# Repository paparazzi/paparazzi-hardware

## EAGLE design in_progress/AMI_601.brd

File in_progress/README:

This directory contains in progress project an some finished development board I made to test different parts

adxrs300_breakout.sch : breakout board for adxrs300 gyro evaluation
AMI_601.sch : breakout board for AMI601 magnetometer
current_probe.sch : some current sensor I don't remember about
ir_single_long.sch
ir_single_slim.sch
lipo_connector.sch
olimex_add_on.sch
pth_supply.sch
pth_supply_servos_molex.sch
pth_supply_servos.sch
test_2620.sch
test_filter.sch
test_usb_hub.sch
tiny4l_18_1_99.sch
vor_add_on.sch
xbee.sch

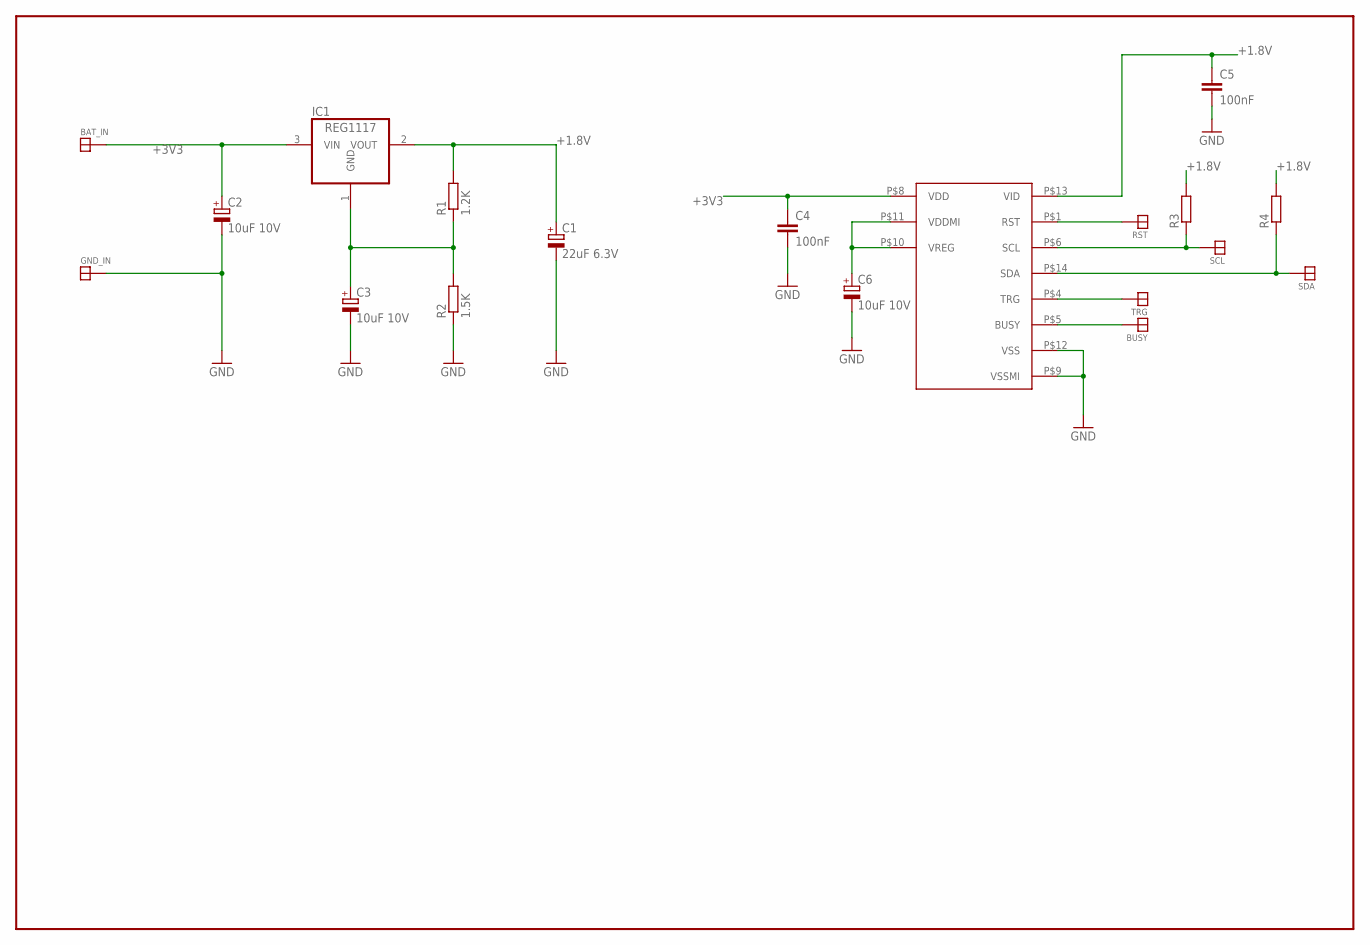
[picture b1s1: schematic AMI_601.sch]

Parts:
BAT_IN: SOLDER_PAD150_75; SOLD_PAD_150_75
BUSY: SOLDER_PAD150_75; SOLD_PAD_150_75
C1: 22uF 6.3V; CT3528
C2, C3, C6: 10uF 10V; CT3216
C4, C5: 100nF; C0805K
GND_IN: SOLDER_PAD150_75; SOLD_PAD_150_75
IC1: REG1117; SOT223
R1: 1.2K; M0805
R2: 1.5K; M0805
R3, R4: R-EU_M0805; M0805
RST: SOLDER_PAD150_75; SOLD_PAD_150_75
SCL: SOLDER_PAD150_75; SOLD_PAD_150_75
SDA: SOLDER_PAD150_75; SOLD_PAD_150_75
TRG: SOLDER_PAD150_75; SOLD_PAD_150_75
U$1: AMI601; AMI_601

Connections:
+1.8V: C1.+, C5.1, IC1.2 (VOUT), R1.2, R3.2, R4.2, U$1.P$13 (VID)
+3V3: BAT_IN.P$1, C2.+, C4.1, IC1.3 (VIN), U$1.P$8 (VDD)
GND: C1.-, C2.-, C3.-, C4.2, C5.2, C6.-, GND_IN.P$1, R2.1, U$1.P$9 (VSSMI), U$1.P$12 (VSS)
unnamed: C3.+, IC1.1 (GND), R1.1, R2.2
unnamed: C6.+, U$1.P$10 (VREG), U$1.P$11 (VDDMI)
unnamed: RST.P$1, U$1.P$1 (RST)
unnamed: R3.1, SCL.P$1, U$1.P$6 (SCL)
unnamed: R4.1, SDA.P$1, U$1.P$14 (SDA)
unnamed: TRG.P$1, U$1.P$4 (TRG)
unnamed: BUSY.P$1, U$1.P$5 (BUSY)

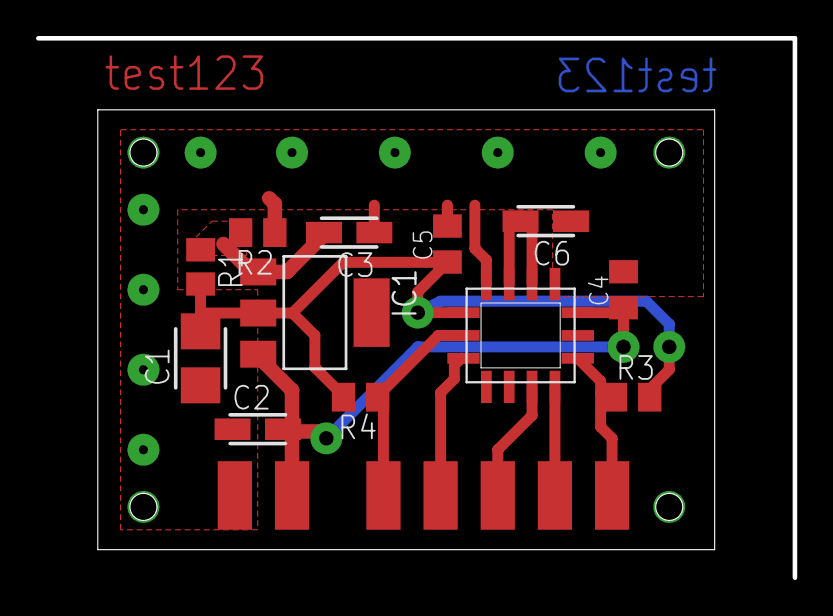
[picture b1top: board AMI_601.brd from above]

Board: 2 copper layers, 34.3 x 24.4 mm, 19 parts (0 on the bottom side), 10 nets.

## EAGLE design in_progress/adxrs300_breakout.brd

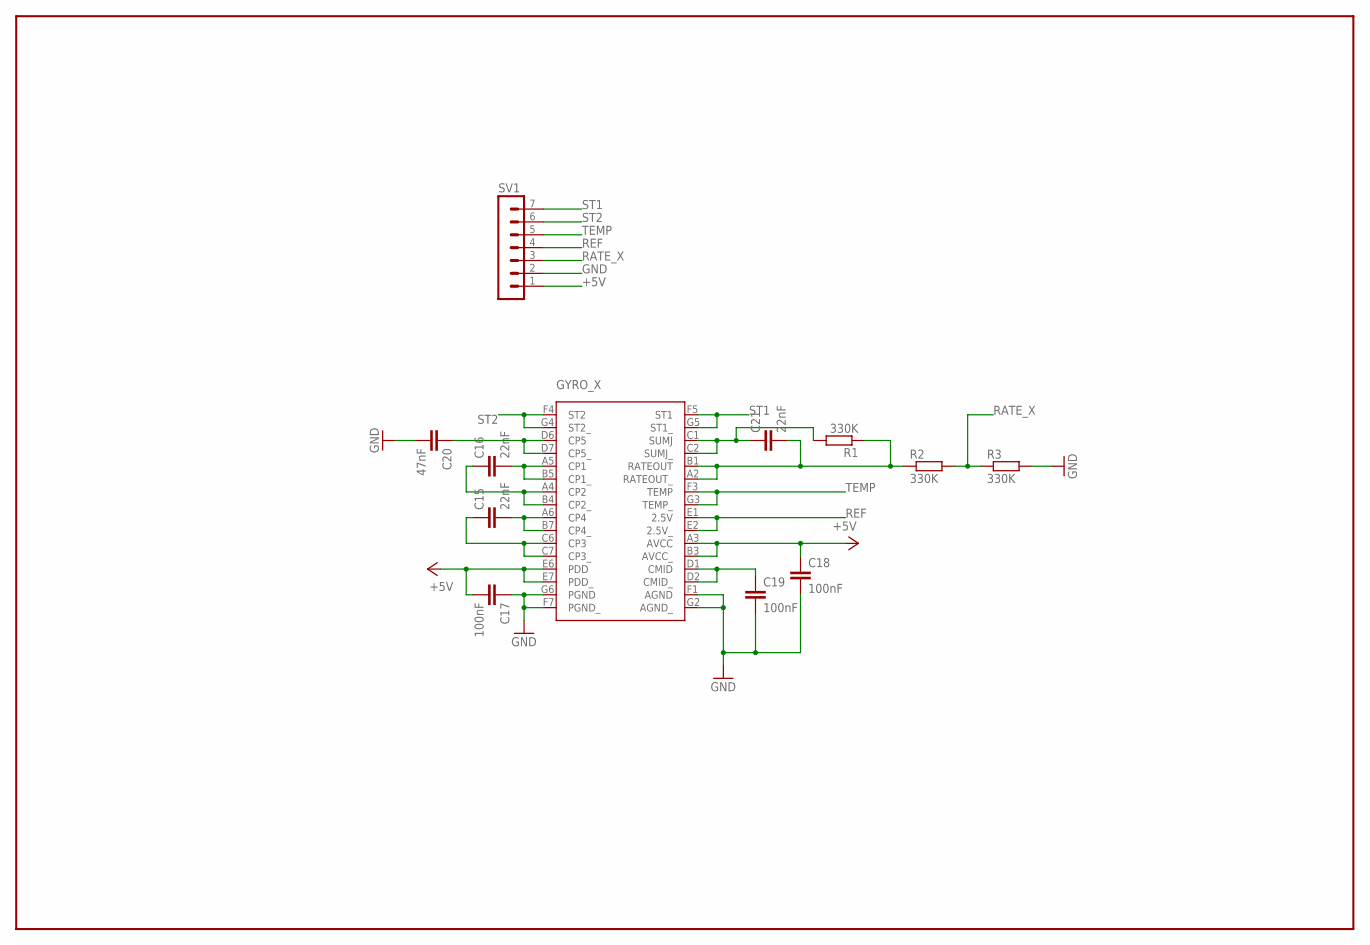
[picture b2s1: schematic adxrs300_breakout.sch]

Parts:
C15, C16, C21: 22nF; C0603K
C17, C18, C19: 100nF; C0603K
C20: 47nF; C0603K
GYRO_X: ADXR; BC-32
R1, R2, R3: 330K; R0603
SV1: MA07-1

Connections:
+5V: C17.2, C18.1, GYRO_X.A3 (AVCC), GYRO_X.B3 (AVCC_), GYRO_X.E6 (PDD), GYRO_X.E7 (PDD_), SV1.1
GND: C17.1, C18.2, C19.2, C20.2, GYRO_X.F1 (AGND), GYRO_X.F7 (PGND_), GYRO_X.G2 (AGND_), GYRO_X.G6 (PGND), R3.2, SV1.2
unnamed: C21.1, GYRO_X.C1 (SUMJ), GYRO_X.C2 (SUMJ_), R1.2
unnamed: C15.1, GYRO_X.C6 (CP3), GYRO_X.C7 (CP3_)
unnamed: C20.1, GYRO_X.D6 (CP5), GYRO_X.D7 (CP5_)
unnamed: C16.2, GYRO_X.A5 (CP1), GYRO_X.B5 (CP1_)
unnamed: C16.1, GYRO_X.A4 (CP2), GYRO_X.B4 (CP2_)
unnamed: C15.2, GYRO_X.A6 (CP4), GYRO_X.B7 (CP4_)
unnamed: C19.1, GYRO_X.D1 (CMID), GYRO_X.D2 (CMID_)
RATE_5V: C21.2, GYRO_X.A2 (RATEOUT_), GYRO_X.B1 (RATEOUT), R1.1, R2.1
RATE_X: R2.2, R3.1, SV1.3
REF: GYRO_X.E1 (2.5V), GYRO_X.E2 (2.5V_), SV1.4
ST1: GYRO_X.F5 (ST1), GYRO_X.G5 (ST1_), SV1.7
ST2: GYRO_X.F4 (ST2), GYRO_X.G4 (ST2_), SV1.6
TEMP: GYRO_X.F3 (TEMP), GYRO_X.G3 (TEMP_), SV1.5

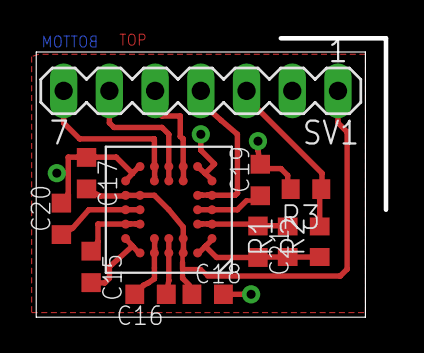
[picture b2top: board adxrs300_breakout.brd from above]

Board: 4 copper layers, 19.4 x 15.5 mm, 12 parts (0 on the bottom side), 15 nets.

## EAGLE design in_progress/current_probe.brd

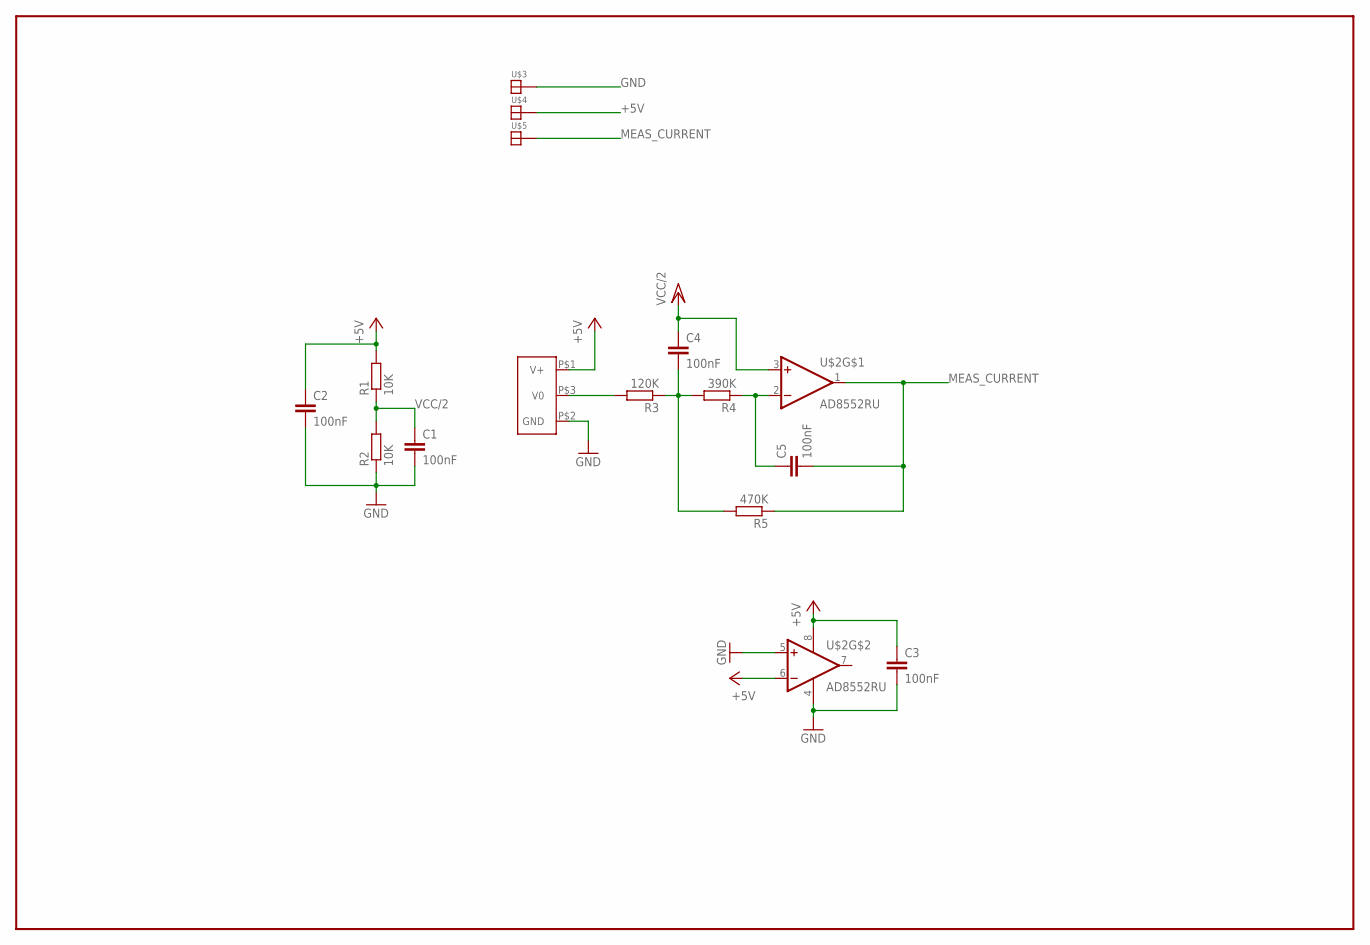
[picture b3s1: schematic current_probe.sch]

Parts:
C1, C2, C3, C4, C5: 100nF; C0603K
R1, R2: 10K; R0603
R3: 120K; R0603
R4: 390K; R0603
R5: 470K; R0603
U$1: SS495S; SS495SND
U$2: AD8552RU; TSSOP8
U$3, U$4, U$5: SOLDER_PAD100_50; SOLDER_PAD_100_50

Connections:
+5V: C2.1, C3.1, R1.2, U$1.P$1 (V+), U$2.6 (-IN), U$2.8 (V+), U$4.P$1
GND: C1.2, C2.2, C3.2, R2.1, U$1.P$2 (GND), U$2.4 (V-), U$2.5 (+IN), U$3.P$1
MEAS_CURRENT: C5.2, R5.1, U$2.1 (OUT), U$5.P$1
unnamed: R3.2, U$1.P$3 (V0)
unnamed: C4.2, R3.1, R4.2, R5.2
unnamed: C5.1, R4.1, U$2.2 (-IN)
VCC/2: C1.1, C4.1, R1.1, R2.2, U$2.3 (+IN)

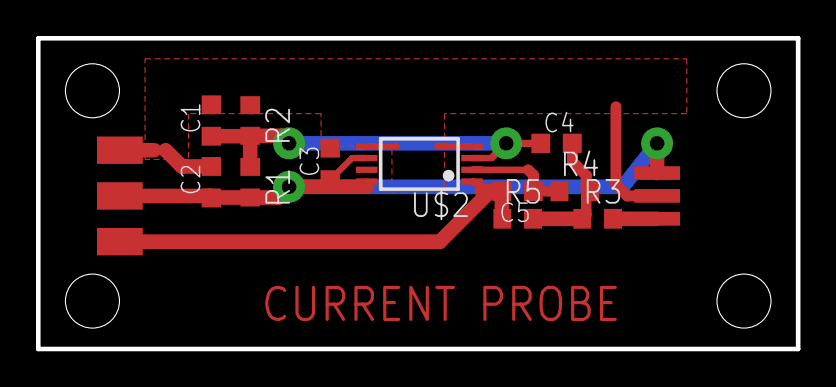
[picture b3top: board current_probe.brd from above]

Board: 2 copper layers, 42.2 x 17.3 mm, 15 parts (0 on the bottom side), 7 nets.

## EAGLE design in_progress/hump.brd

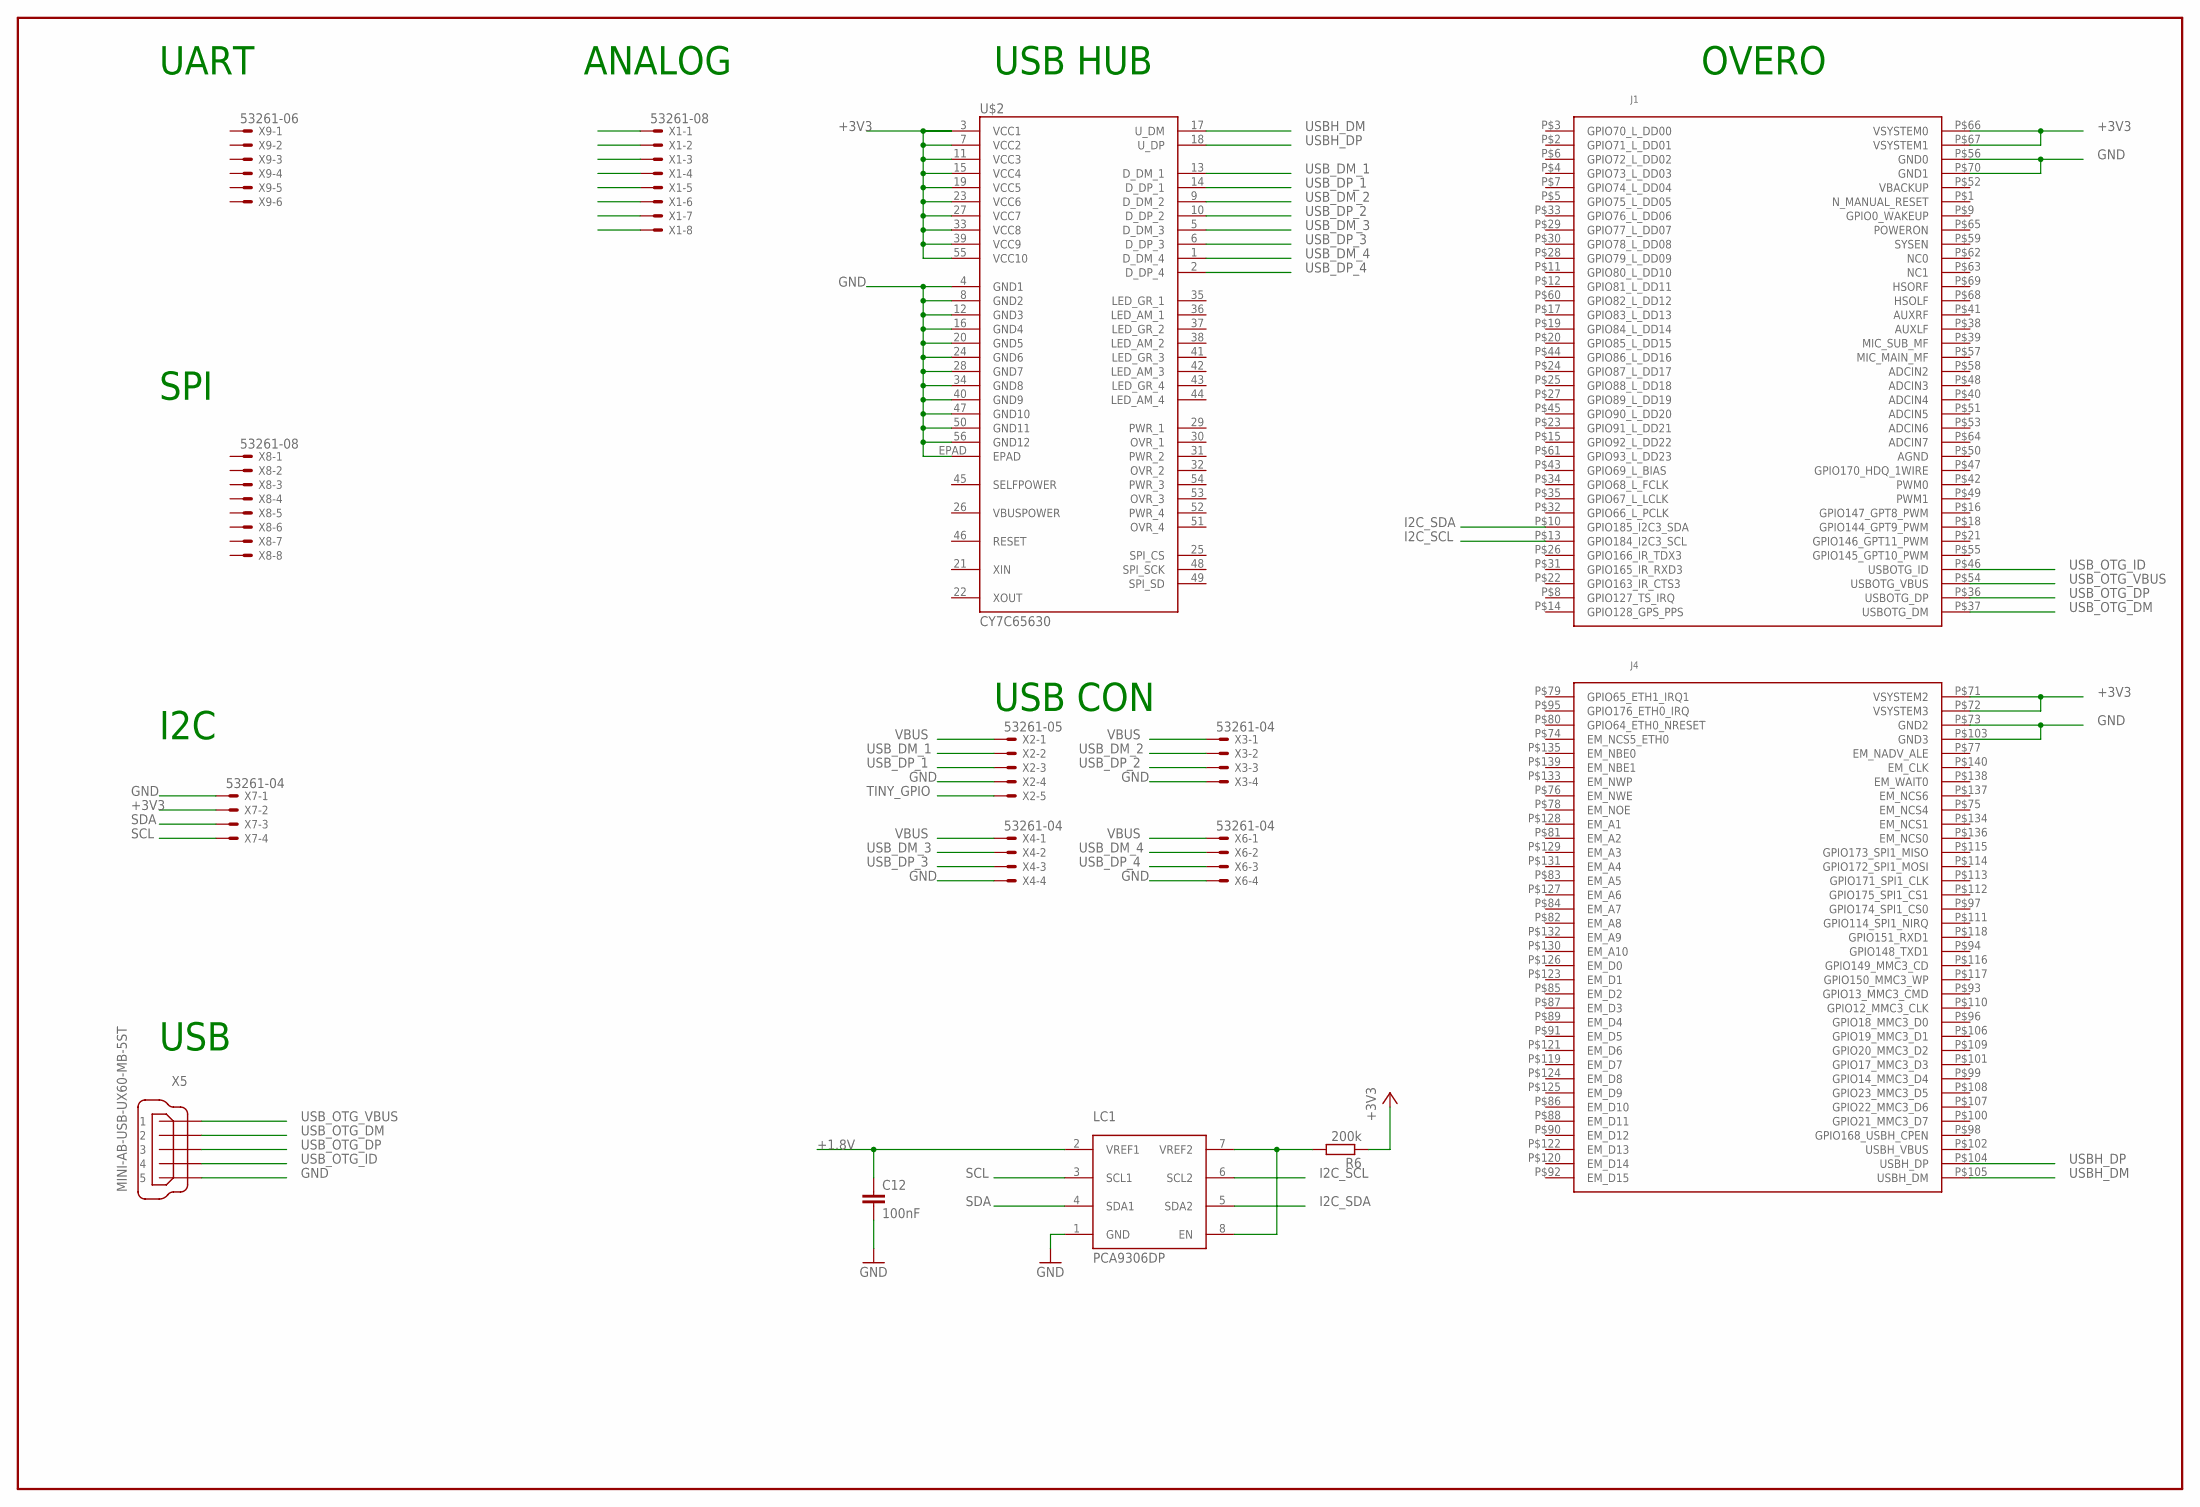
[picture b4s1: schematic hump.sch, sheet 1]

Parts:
C12: 100nF; C0603
LC1: PCA9306DP; TSSOP_B3
R6: 200k; R0603
U$1: CON_OVERO
U$2: CY7C65630; QFN56
X1, X8: 53261-08
X2: 53261-05
X3, X4, X6, X7: 53261-04
X5: MINI-AB-USB-UX60-MB-5ST; UX60-MB-5ST
X9: 53261-06

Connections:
+1.8V: C12.1, LC1.2 (VREF1)
+3V3: R6.1, U$1.P$66 (VSYSTEM0), U$1.P$67 (VSYSTEM1), U$1.P$71 (VSYSTEM2), U$1.P$72 (VSYSTEM3), U$2.3 (VCC1), U$2.7 (VCC2), U$2.11 (VCC3), U$2.15 (VCC4), U$2.19 (VCC5), U$2.23 (VCC6), U$2.27 (VCC7), U$2.33 (VCC8), U$2.39 (VCC9), U$2.55 (VCC10), X7.2
GND: C12.2, LC1.1 (GND), U$1.P$56 (GND0), U$1.P$70 (GND1), U$1.P$73 (GND2), U$1.P$103 (GND3), U$2.4 (GND1), U$2.8 (GND2), U$2.12 (GND3), U$2.16 (GND4), U$2.20 (GND5), U$2.24 (GND6), U$2.28 (GND7), U$2.34 (GND8), U$2.40 (GND9), U$2.47 (GND10), U$2.50 (GND11), U$2.56 (GND12), U$2.EPAD, X1.1, X2.4, X3.4, X4.4, X5.5, X6.4, X7.1; also elsewhere on the board
I2C_SCL: LC1.6 (SCL2), U$1.P$13 (GPIO184_I2C3_SCL)
I2C_SDA: LC1.5 (SDA2), U$1.P$10 (GPIO185_I2C3_SDA)
unnamed: LC1.7 (VREF2), LC1.8 (EN), R6.2
SCL: LC1.3 (SCL1), X7.4
SDA: LC1.4 (SDA1), X7.3
TINY_GPIO: X2.5
USBH_DM: U$1.P$105 (USBH_DM), U$2.17 (U_DM)
USBH_DP: U$1.P$104 (USBH_DP), U$2.18 (U_DP)
USB_DM_1: U$2.13 (D_DM_1), X2.2
USB_DM_2: U$2.9 (D_DM_2), X3.2
USB_DM_3: U$2.5 (D_DM_3), X4.2
USB_DM_4: U$2.1 (D_DM_4), X6.2
USB_DP_1: U$2.14 (D_DP_1), X2.3
USB_DP_2: U$2.10 (D_DP_2), X3.3
USB_DP_3: U$2.6 (D_DP_3), X4.3
USB_DP_4: U$2.2 (D_DP_4), X6.3
USB_OTG_DM: U$1.P$37 (USBOTG_DM), X5.2
USB_OTG_DP: U$1.P$36 (USBOTG_DP), X5.3
USB_OTG_ID: U$1.P$46 (USBOTG_ID), X5.4
USB_OTG_VBUS: U$1.P$54 (USBOTG_VBUS), X5.1
VBUS: X2.1, X3.1, X4.1, X6.1

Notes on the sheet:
OVERO
UART
SPI
I2C
USB
ANALOG
USB HUB
USB CON

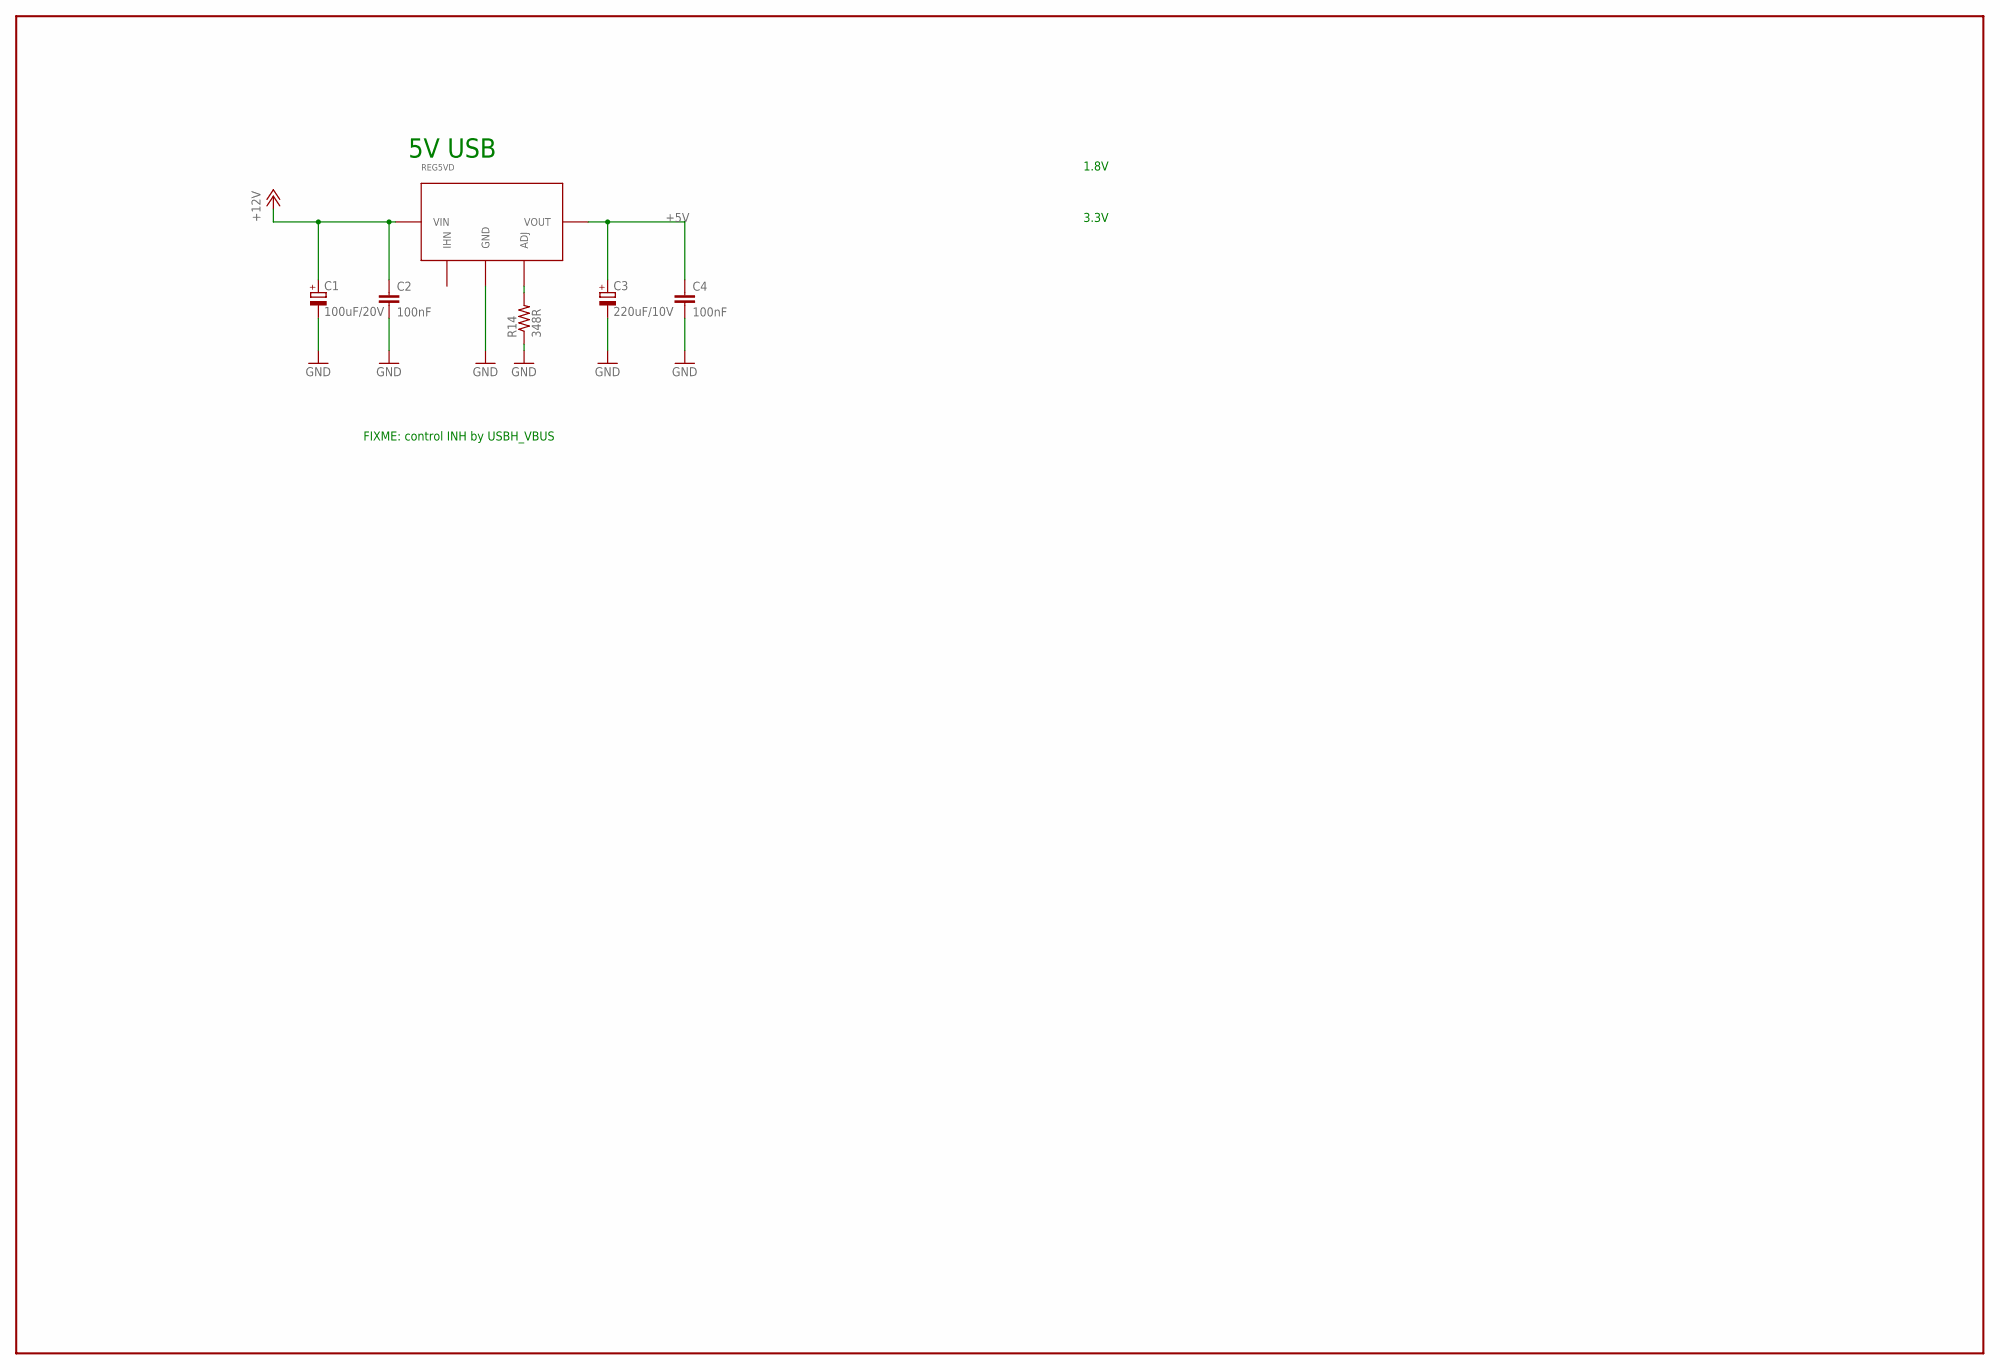
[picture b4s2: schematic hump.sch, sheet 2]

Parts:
C1: 100uF/20V; SMC_D
C2, C4: 100nF; C0603
C3: 220uF/10V; SMC_D
R14: 348R; R0603
REG5VD: PTHTH; PTH_TH

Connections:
+5V: C3.+, C4.1, REG5VD.P$3 (VOUT)
+12V: C1.+, C2.1, REG5VD.P$1 (VIN)
GND: C1.-, C2.2, C3.-, C4.2, R14.1, REG5VD.P$2 (GND); also elsewhere on the board
unnamed: R14.2, REG5VD.P$4 (ADJ)

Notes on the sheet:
5V USB
FIXME: control INH by USBH_VBUS
1.8V
3.3V

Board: 2 copper layers, 20 parts (0 on the bottom side), 26 nets, no tracks yet.

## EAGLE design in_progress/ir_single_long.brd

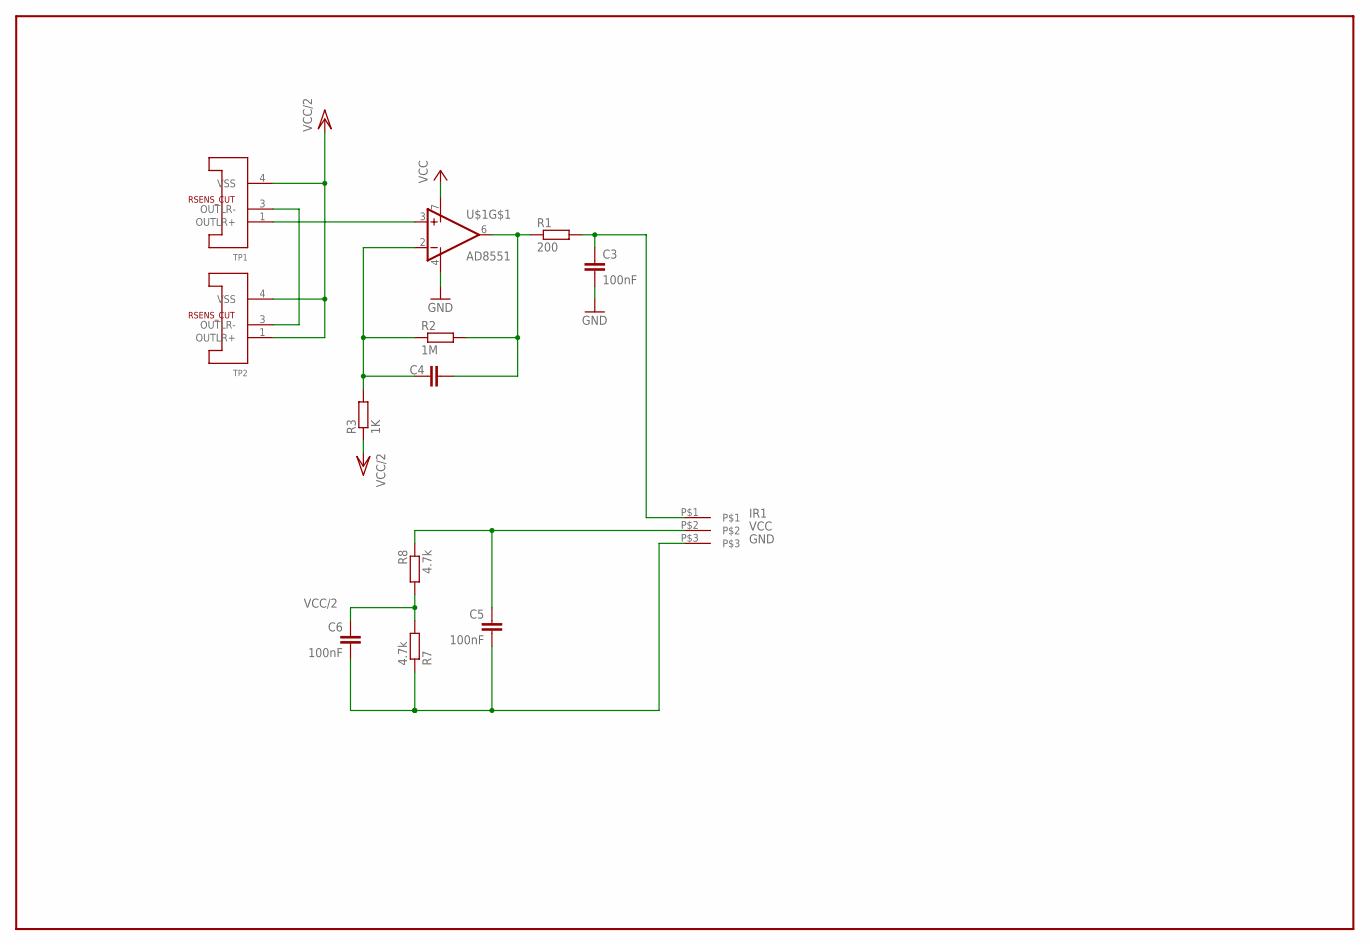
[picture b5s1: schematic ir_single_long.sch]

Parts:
C3: 100nF; C1206K
C4: C-EUC0603; C0603
C5, C6: 100nF; C0603
R1: 200; R0603
R2: 1M; R0603
R3: 1K; R0603
R7, R8: 4.7k; R0603
TP1, TP2: MLX90247SMD_LONG; T0_39_SMD_LONG
U$1: AD8551; MSOP8
U$2: SOLD_PAD_3; SOLD_PAD_2MM_3

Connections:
GND: C3.2, C5.2, C6.2, R7.1, U$1.4 (V-), U$2.P$3
IR1: C3.1, R1.2, U$2.P$1
unnamed: TP1.3 (OUTLR-), TP2.3 (OUTLR-)
unnamed: C4.2, R1.1, R2.2, U$1.6 (OUT)
unnamed: TP1.1 (OUTLR+), U$1.3 (+IN)
unnamed: C4.1, R2.1, R3.2, U$1.2 (-IN)
VCC: C5.1, R8.1, U$1.7 (V+), U$2.P$2
VCC/2: C6.1, R3.1, R7.2, R8.2, TP1.4 (VSS), TP2.1 (OUTLR+), TP2.4 (VSS)

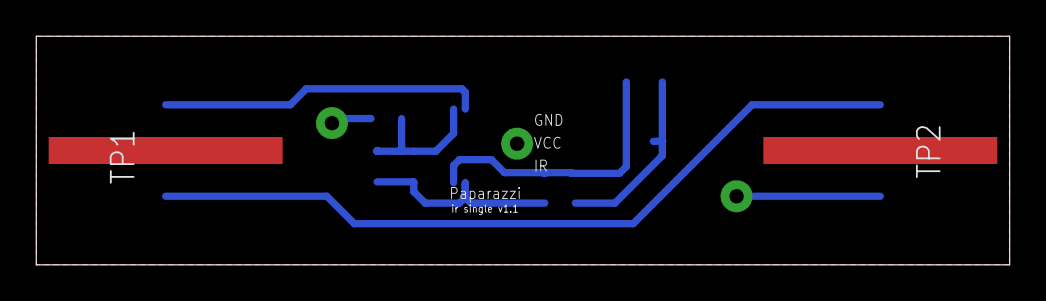
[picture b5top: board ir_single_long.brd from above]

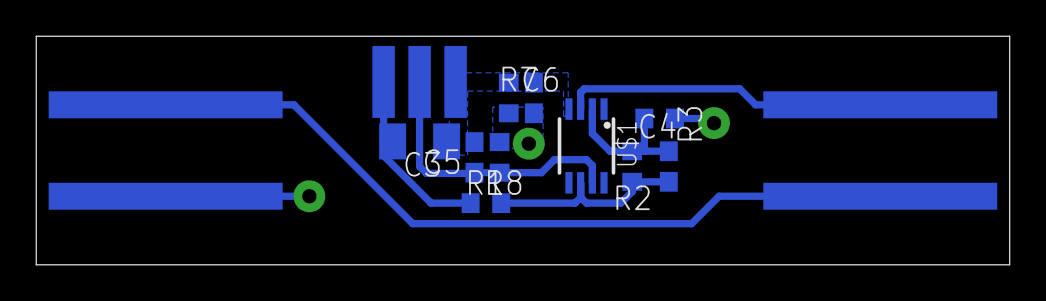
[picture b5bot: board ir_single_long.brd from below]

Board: 2 copper layers, 54.1 x 12.7 mm, 13 parts (11 on the bottom side), 8 nets.

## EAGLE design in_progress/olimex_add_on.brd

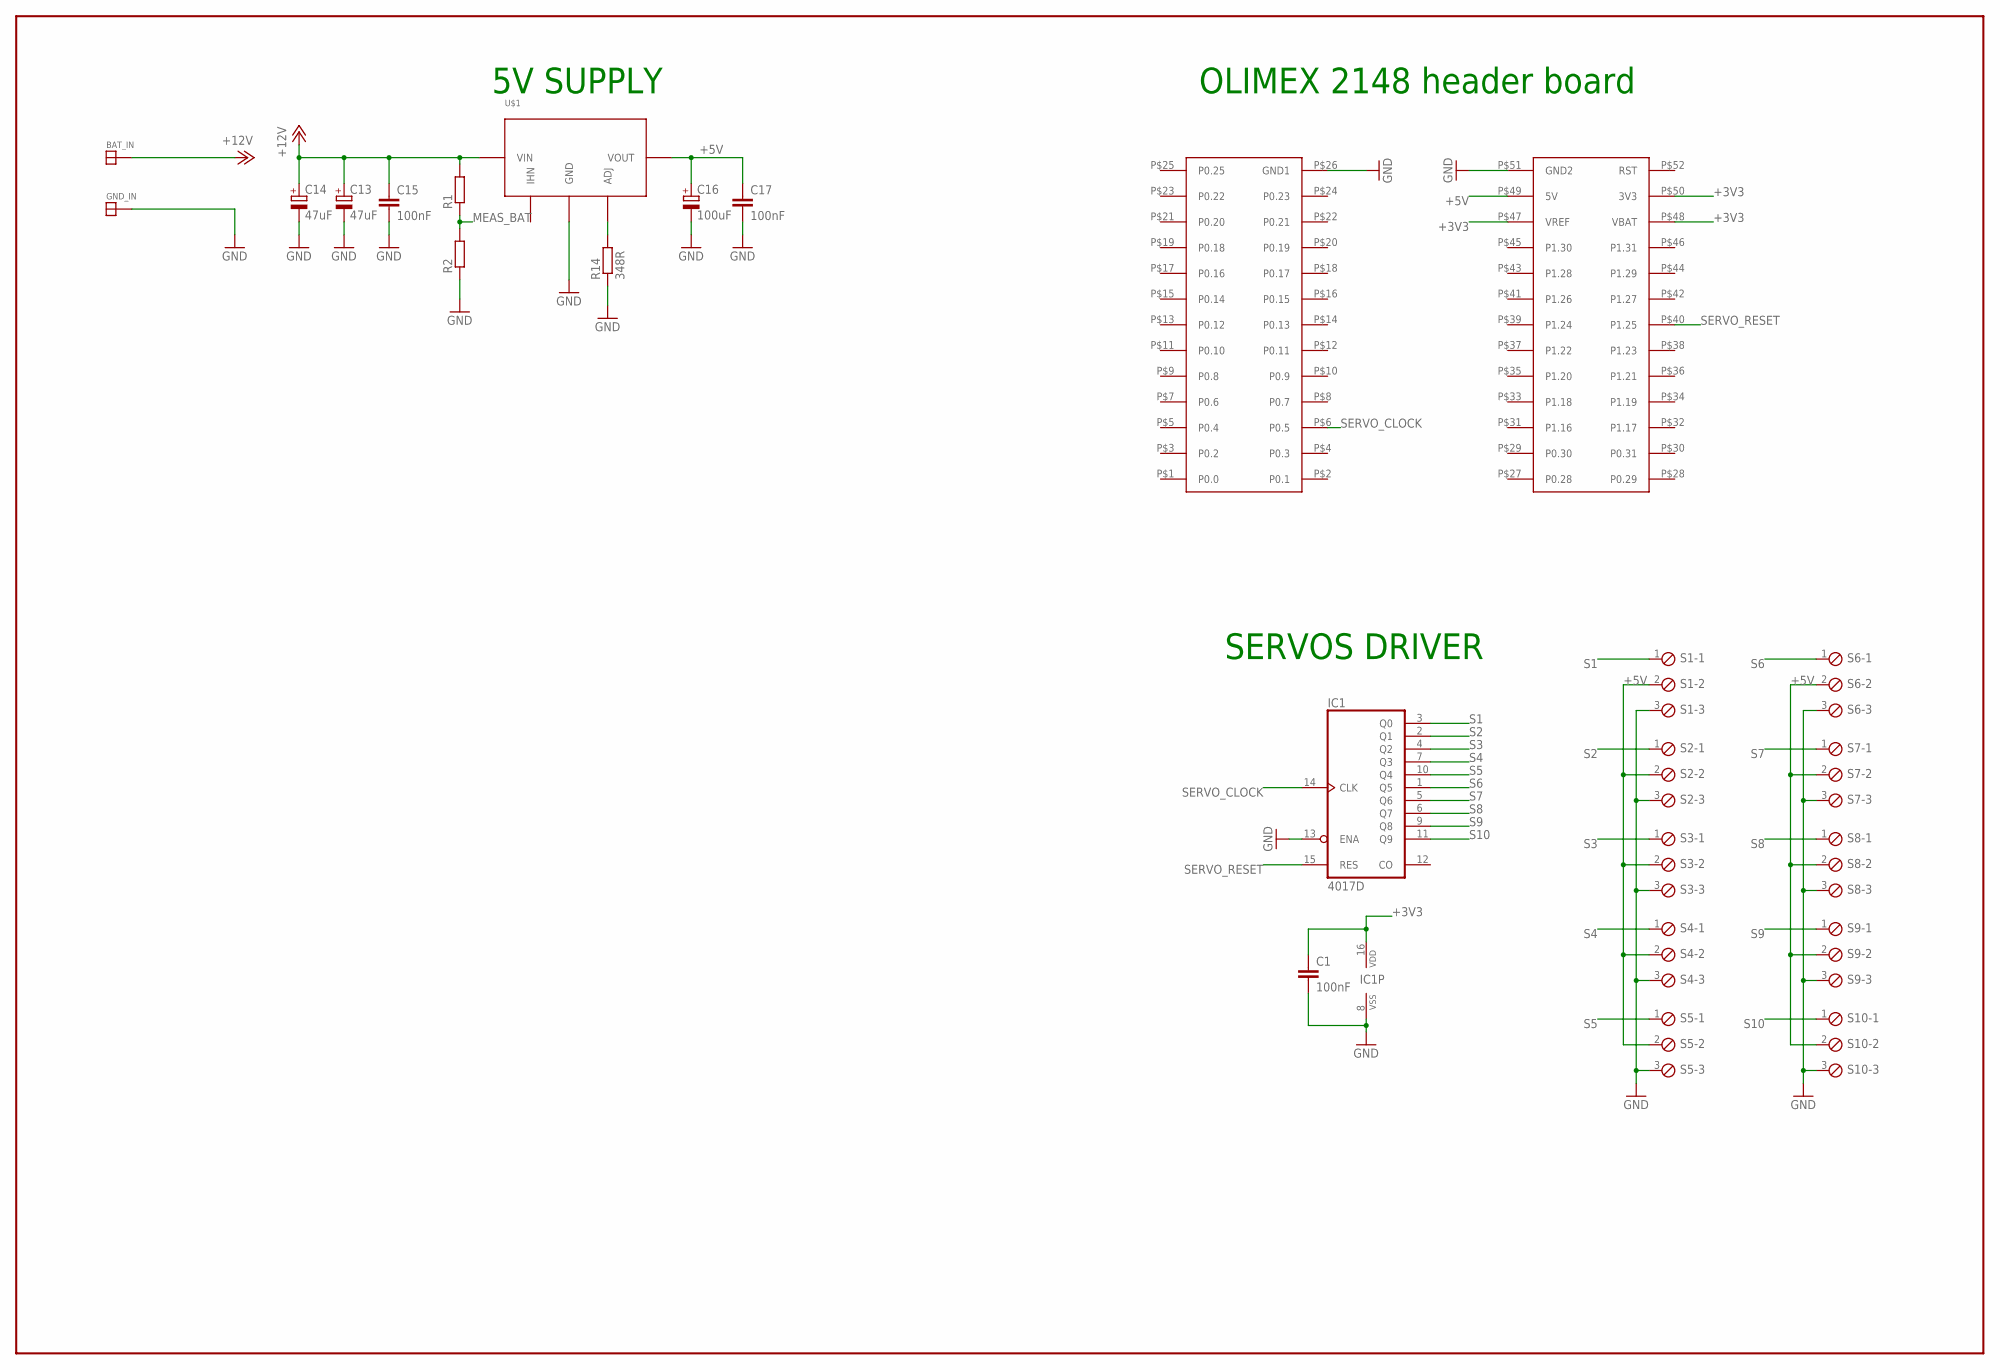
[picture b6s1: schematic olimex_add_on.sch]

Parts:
BAT_IN: SOLDER_PAD150_75; SOLD_PAD_150_75
C1: 100nF; C0805K
C13, C14: 47uF; SMC_D
C15, C17: 100nF; C1206K
C16: 100uF; SMC_D
GND_IN: SOLDER_PAD150_75; SOLD_PAD_150_75
IC1: 4017D; SO16
R1, R2: R-EU_R0805; R0805
R14: 348R; R0805
S1, S2, S3, S4, S5, S6, S7, S8, S9, S10: MPT3; 3POL254
U$1: PTH
U$5: OLIMEX_2148

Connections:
+3V3: C1.1, IC1.16 (VDD), U$5.P$47 (VREF), U$5.P$48 (VBAT), U$5.P$50 (3V3)
+5V: C16.+, C17.1, S1.2, S2.2, S3.2, S4.2, S5.2, S6.2, S7.2, S8.2, S9.2, S10.2, U$1.P$3 (VOUT), U$5.P$49 (5V)
+12V: BAT_IN.P$1, C13.+, C14.+, C15.1, R1.2, U$1.P$1 (VIN)
GND: C1.2, C13.-, C14.-, C15.2, C16.-, C17.2, GND_IN.P$1, IC1.8 (VSS), IC1.13 (ENA), R2.1, R14.1, S1.3, S2.3, S3.3, S4.3, S5.3, S6.3, S7.3, S8.3, S9.3, S10.3, U$1.P$2 (GND), U$5.P$26 (GND1), U$5.P$51 (GND2)
MEAS_BAT: R1.1, R2.2
unnamed: R14.2, U$1.P$4 (ADJ)
S1: IC1.3 (Q0), S1.1
S2: IC1.2 (Q1), S2.1
S3: IC1.4 (Q2), S3.1
S4: IC1.7 (Q3), S4.1
S5: IC1.10 (Q4), S5.1
S6: IC1.1 (Q5), S6.1
S7: IC1.5 (Q6), S7.1
S8: IC1.6 (Q7), S8.1
S9: IC1.9 (Q8), S9.1
S10: IC1.11 (Q9), S10.1
SERVO_CLOCK: IC1.14 (CLK), U$5.P$6 (P0.5)
SERVO_RESET: IC1.15 (RES), U$5.P$40 (P1.25)

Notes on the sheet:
5V SUPPLY
SERVOS DRIVER
OLIMEX 2148 header board

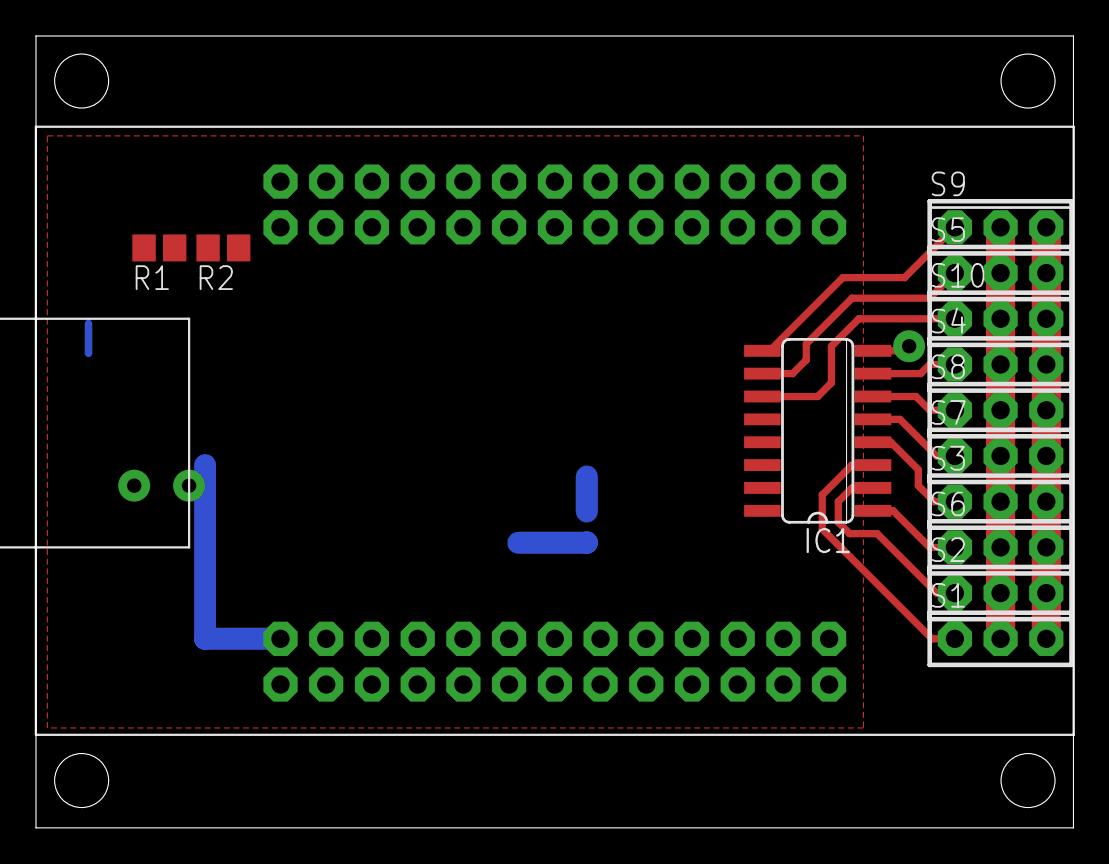
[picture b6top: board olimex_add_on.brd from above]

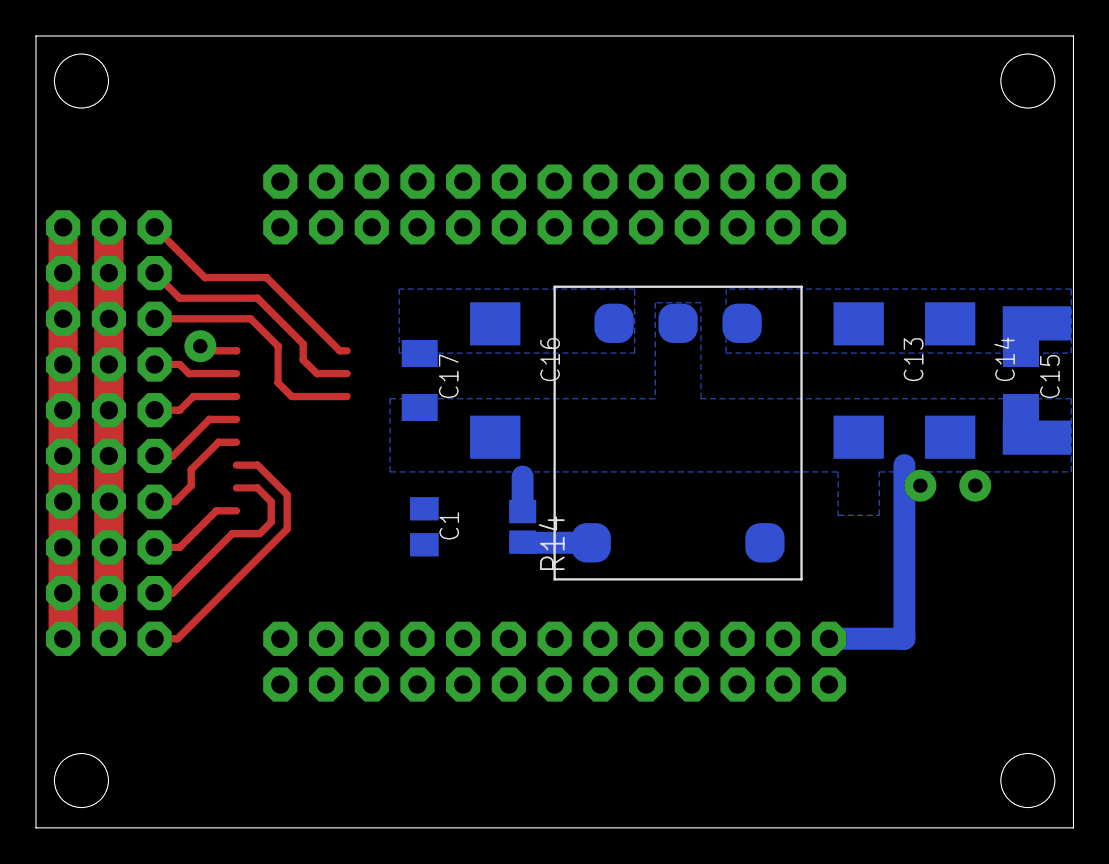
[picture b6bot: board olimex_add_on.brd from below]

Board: 2 copper layers, 57.6 x 44.0 mm, 24 parts (10 on the bottom side), 18 nets.
